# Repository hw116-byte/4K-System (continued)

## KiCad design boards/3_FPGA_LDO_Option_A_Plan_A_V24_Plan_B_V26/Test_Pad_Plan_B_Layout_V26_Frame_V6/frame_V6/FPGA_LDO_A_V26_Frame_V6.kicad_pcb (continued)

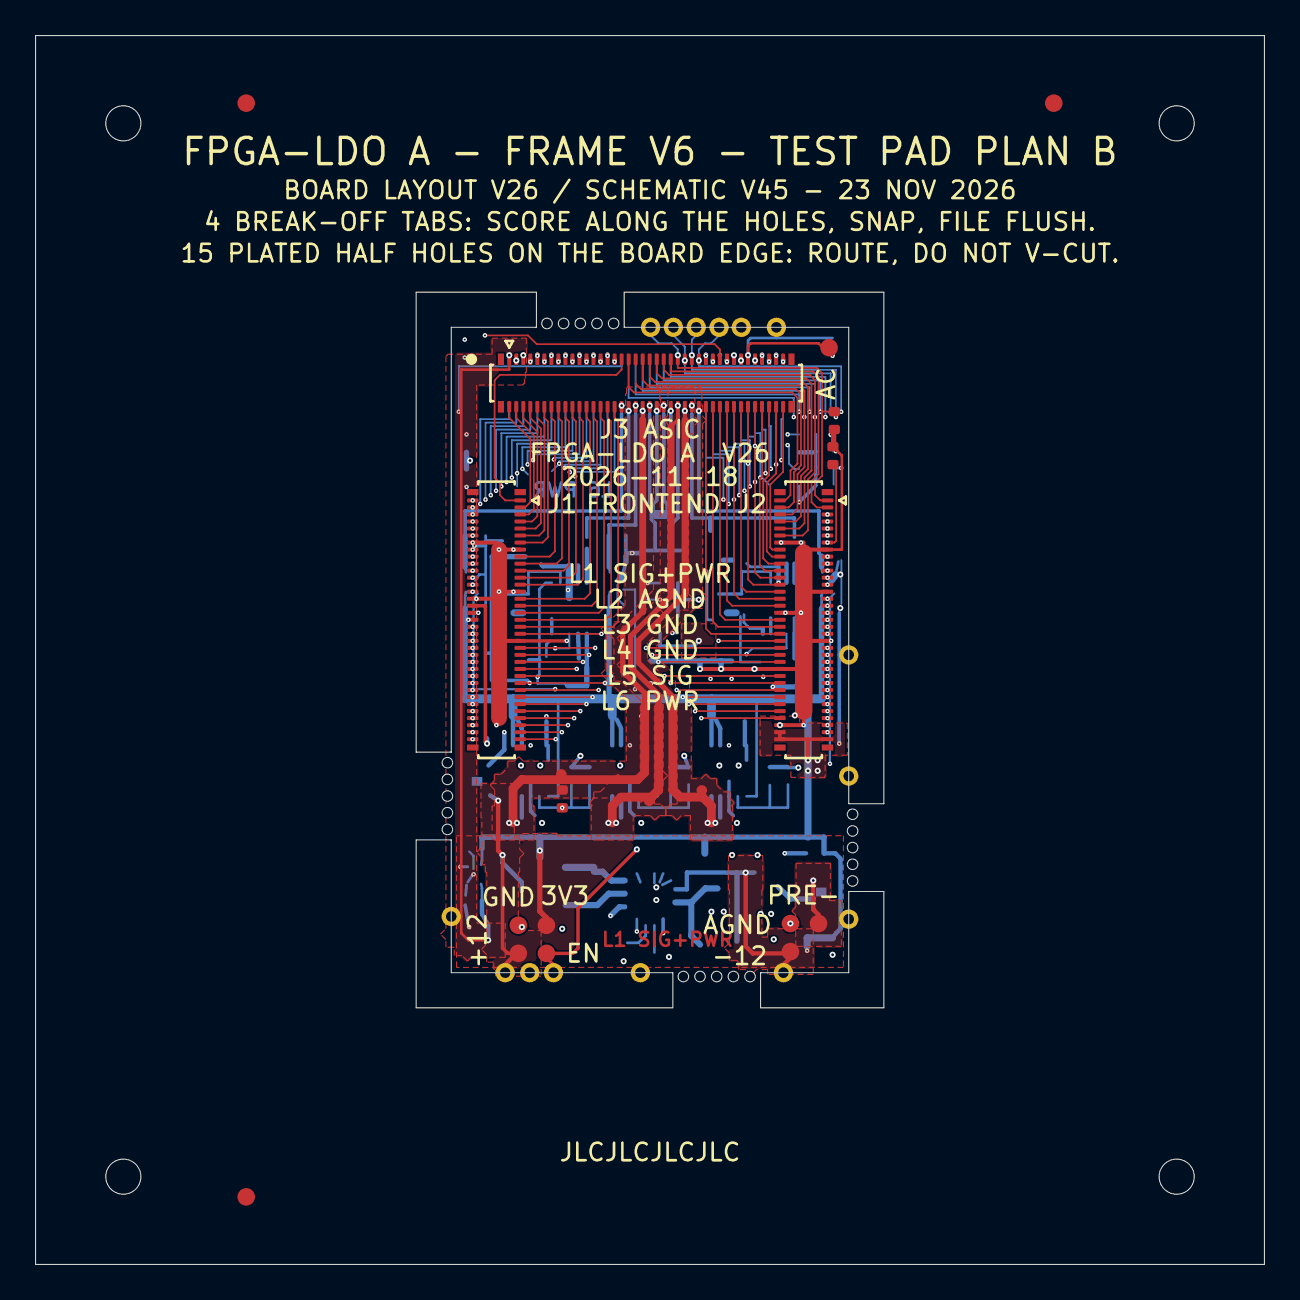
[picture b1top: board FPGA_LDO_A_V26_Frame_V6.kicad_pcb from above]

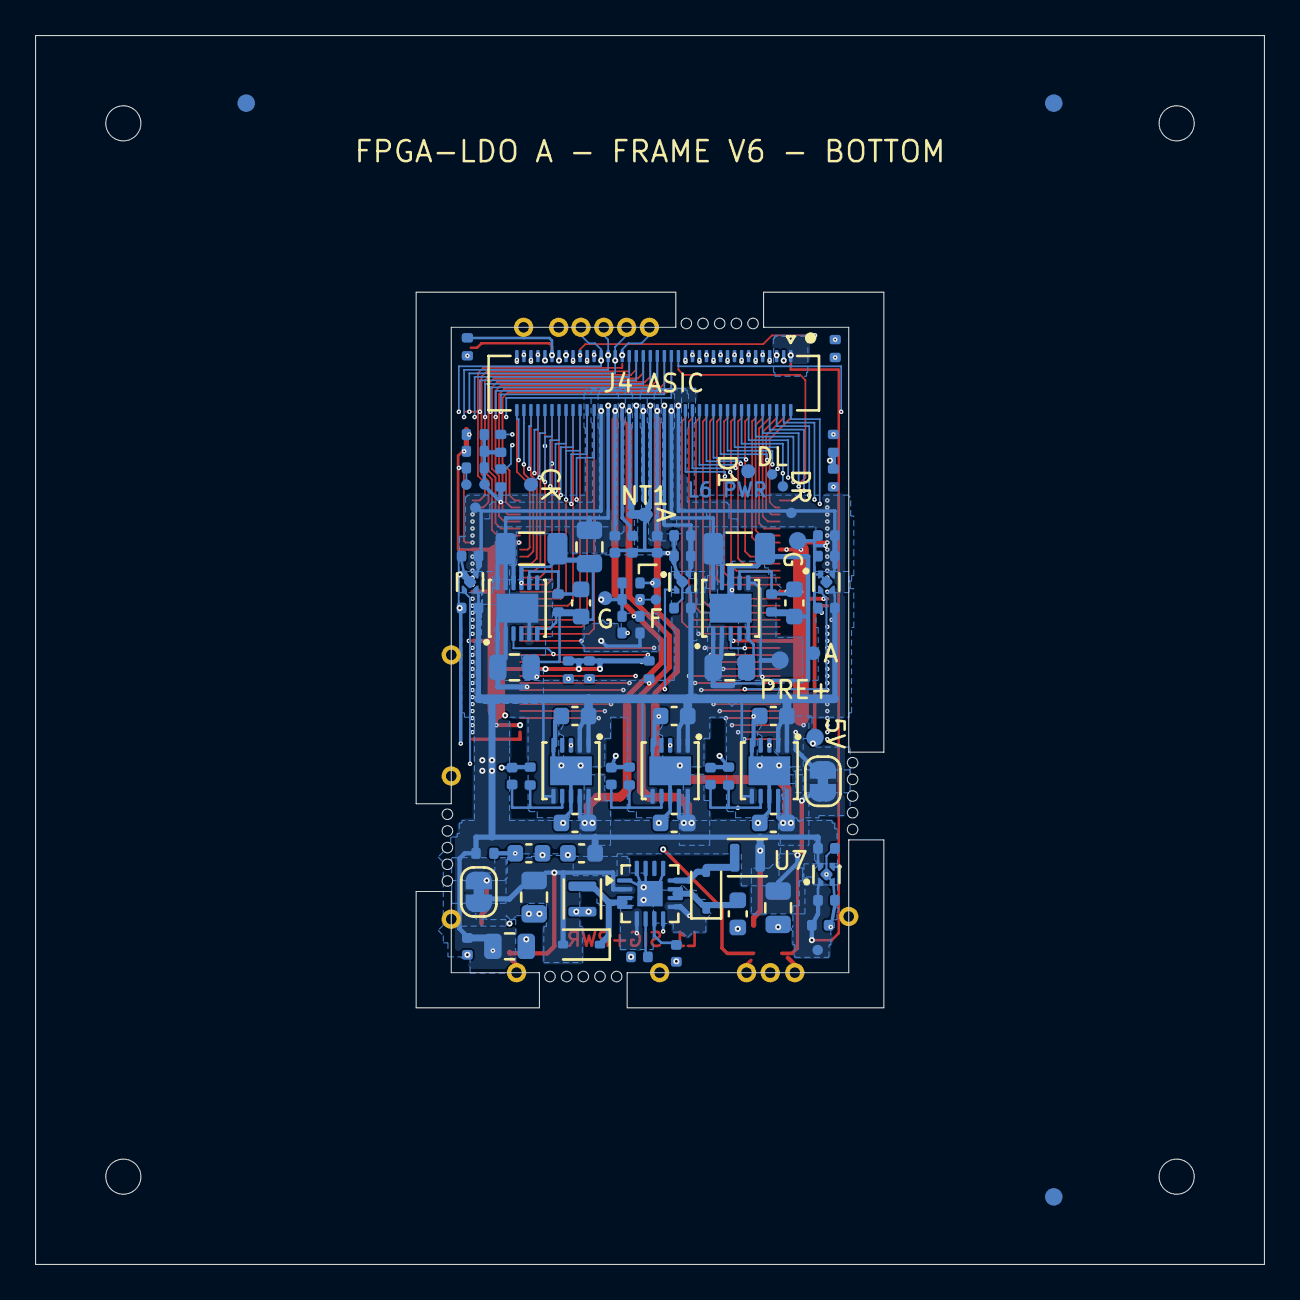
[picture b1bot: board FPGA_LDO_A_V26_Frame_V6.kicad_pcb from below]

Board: 6 copper layers, 70.0 x 70.0 mm, 142 parts (99 on the bottom side), 150 nets.

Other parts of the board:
FID1, FID2, FID3, FID4, FID5, FID6: fiducial 1.0 mm, mask opening 2.0 mm
MB1: mech tab N1, 5 x 0.60 mm holes
MB2: mech tab S1, 5 x 0.60 mm holes
MB3: mech tab W1, 5 x 0.60 mm holes
MB4: mech tab E1, 5 x 0.60 mm holes
TH1, TH2, TH3, TH4: tooling hole 2.0 mm, not plated

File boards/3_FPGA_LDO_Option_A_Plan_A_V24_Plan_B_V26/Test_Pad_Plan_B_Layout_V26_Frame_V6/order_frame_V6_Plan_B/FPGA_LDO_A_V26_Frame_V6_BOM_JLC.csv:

Comment,Designator,Footprint,JLCPCB Part #,Qty,Note
Samsung CL21A226MAYNNNE 22uF 25V X5R 0805,"C1,C14,C21",C_0805_2012Metric,C602037,3,
Samsung CL05B104KB54PNC 100nF 50V X7R 0402,C2,C_0402_1005Metric,C307331,1,
Samsung CL10A475KP8NNNC 4.7uF 10V X5R 0603,"C3,C11",C_0603_1608Metric,C1705,2,
Samsung CL10A105KA8NNNC 1uF 25V X5R 0603,"C15,C903,C1003",C_0603_1608Metric,C5673,3,
Samsung CL05B103KB5NNNC 10nF 50V X7R 0402,"C16,C17",C_0402_1005Metric,C15195,2,
Samsung CL05A105KP5NNNC 1uF 10V X5R 0402,"C51,C53,C54,C55,C56,C57,C203,C301,C302,C401,C402,C501,C502,C603,C701,C702,C803",C_0402_1005Metric,C14445,17,
Samsung CL10A106KP8NNNC 10uF 10V X5R 0603,"C201,C202,C601,C602,C801,C802",C_0603_1608Metric,C19702,6,
Samsung CL21A106KAYNNNE 10uF 25V X5R 0805,"C901,C1001,C1004",C_0805_2012Metric,C15850,3,
Samsung CL31A226KAHNNNE 22uF 25V X5R 1206,"C902,C1002",C_1206_3216Metric,C12891,2,
MCC B0540WS-TP 40V 0.5A Schottky SOD-323,"D11,D12",D_SOD-323,C668860,2,"Schematic V35 names this part (V34 named Diodes Inc. B0540WS-7, C98664, which cannot be ordered at JLC); it is the part of the 11 Nov 2026 cart. JLC library pad 1 is the ANODE for this part: the CPL angle is turned 180 deg against KiCad. Cathode positions are in the pin-1 table."
Hirose DF40C-70DP-0.4V(51),"J1,J2",Hirose_DF40C-70DP-0.4V_2x35-1MP_P0.4mm,C2692097,2,
Hirose DF40C-80DP-0.4V(51),J3,Hirose_DF40C-80DP-0.4V_2x40-1MP_P0.4mm,C294544,1,
Hirose DF40C-80DS-0.4V(51),J4,Hirose_DF40C-80DS-0.4V_2x40_P0.4mm,C312960,1,
TDK VLS201612HBX-6R8M-1 6.8uH 2.0x1.6x1.2mm,"L11,L12",L_Murata_DFE201610P,C501945,2,"Schematic V35 names this part (V34 named Murata DFE201610E-6R8M=P2, no JLC listing); it is the part of the 11 Nov 2026 cart. Isat 0.91 A, 1.2 mm high."
Uniroyal 0402WGF1002TCE 10k 1% 0402,"R1,R2,R3,R4,R5,R6,R16,R17,R18,R19,R20,R21,R22,R23,R24,R25,R26,R27,R28",R_0402_1005Metric,C25744,19,"R28 is new in layout V24: 10k from BOARD3_SPI_LATCH to GND, bottom side; the same part as R16-R27. JLC Basic part."
Uniroyal 0402WGF1502TCE 15k 1% 0402,"R201,R601",R_0402_1005Metric,C25756,2,
Uniroyal 0402WGF7501TCE 7.5k 1% 0402,R801,R_0402_1005Metric,C25918,1,
Uniroyal 0402WGF8062TCE 80.6k 1% 0402,"R901,R1001",R_0402_1005Metric,C25921,2,
Analog Devices LT3582EUD-12#PBF,U1,QFN-16-1EP_3x3mm_P0.5mm_EP1.45x1.45mm,C670975,1,Only the -12 version is acceptable (LT3582EUD-12#PBF or #TRPBF); no base LT3582 and no -5.
"Analog Devices LT3042EDD#TRPBF (same part as LT3042EDD#PBF, on tape and reel)","U2,U6,U8,U9",DFN-10-1EP_3x3mm_P0.5mm_EP1.65x2.38mm,C580010,4,
Texas Instruments TPS7A2015PDQNR,"U3,U4,U5,U7",Texas_X2SON-4_1x1mm_P0.65mm,C2862700,4,
Analog Devices LT3094EDD#PBF,U10,DFN-12-1EP_3x3mm_P0.45mm_EP1.65x2.38mm,C670492,1,
Uniroyal 0402WGF4702TCE 47k 1% 0402,R802,R_0402_1005Metric,C25792,1,"New in layout V22: minimum load of U8 (LT3042, 0.75 V REF_VCM), from ASIC_REF_VCM to AGND. JLC Basic part."

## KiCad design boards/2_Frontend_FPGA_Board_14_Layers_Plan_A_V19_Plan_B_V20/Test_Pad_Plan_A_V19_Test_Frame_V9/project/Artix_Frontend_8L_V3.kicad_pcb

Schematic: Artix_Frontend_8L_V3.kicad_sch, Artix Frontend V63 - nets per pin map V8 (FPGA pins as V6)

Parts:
C1, C2, C12, C13, C21, C22, C85, C86: 22uF; C_0603_1608Metric; Voltage 6.3 V; Tolerance 20%; MPN GRM188R60J226MEA0D; LCSC C77042
C3, C14, C23, C87: 22pF; C_0201_GRM03_Murata_0p22Gap; Voltage 50 V; Tolerance 2%; MPN GRM0335C1H220GA01D; LCSC C161417
C4, C89: 100uF; C_0805_2012Metric; Voltage 6.3 V; Tolerance 20%; MPN GRM21BR60J107ME15L; not fitted
C5, C6, C25, C36, C37, C51, C54, C96, C107: 4.7uF; C_0201_GRM03_Murata_0p22Gap; Voltage 6.3 V; Tolerance 20%; MPN GRM035R60J475ME15D; LCSC C335103
C7, C8, C9, C11, C18, C19, C20, C26, C27, C28, C29, C32, C33, C34, C35, C38, C39, C40, C52, C53, C55, C56, C57, C58, C80, C91, C92, C93, C97, C98, C99, C100: 470nF; C_0201_GRM03_Murata_0p22Gap; Voltage 6.3 V; Tolerance 20%; MPN GRM033R60J474ME90D; LCSC C88915
C10: 47uF; C_0805_2012Metric; Voltage 6.3 V; Tolerance 20%; MPN GRM21BR60J476ME15L; LCSC C77072
C15: 47uF; C_0805_2012Metric; Voltage 6.3 V; Tolerance 20%; MPN CC0805MKX5R5BB476; LCSC C109461
C16, C17, C24, C30, C31, C43, C44, C45, C47, C48, C49, C90, C94, C95, C101: 4.7uF; C_0402_1005Metric; Voltage 6.3 V; Tolerance 20%; MPN GRM155R60J475ME47D; LCSC C82453
C42: 47uF; C_0805_2012Metric; Voltage 6.3 V; Tolerance 20%; MPN GRM219R60J476ME44D; LCSC C471380
C46, C50: 10nF; C_0201_GRM03_Murata_0p22Gap; Voltage 10 V; Tolerance 10%; MPN GRM033R71A103KA01D; LCSC C76941
C59: 47uF; C_0805_2012Metric; Voltage 6.3 V; Tolerance 20%; MPN CC0805MKX5R5BB476; not fitted
C60, C63, C78, C79, C81, C82, C83, C88, C105, C106, C209: 100nF; C_0201_GRM03_Murata_0p22Gap; Voltage 10 V; Tolerance 10%; MPN GRM033R61A104KE15D; LCSC C76934
C61, C84: 1uF; C_0402_1005Metric; Voltage 10 V; Tolerance 10%; MPN GRM155C81A105KA12D; LCSC C162161
C62: 220nF; C_0201_GRM03_Murata_0p22Gap; Voltage 6.3 V; Tolerance 10%; MPN GRM033R60J224KE15D; LCSC C76931
C75, C76, C102, C104: 22uF / 6.3V; C_0603_1608Metric; Voltage 6.3 V; Tolerance 20%; MPN GRM188R60J226MEA0D; LCSC C77042
C77: 22nF / 16V; C_0201_GRM03_Murata_0p22Gap; Voltage 16V; Tolerance 10%; MPN GRM033R61C223KE84D; LCSC C161473
C103: 470nF / 6.3V; C_0201_GRM03_Murata_0p22Gap; Voltage 6.3 V; Tolerance 20%; MPN GRM033R60J474ME90D; LCSC C88915
C206, C207, C208: 22uF / 10V; C_0805_2012Metric; Voltage 10 V; Tolerance 20%; MPN GRM21BR61A226ME44L; LCSC C441864
J1, J2: DF40C-70DS-0.4V(51); Hirose_DF40C-70DS-0.4V_2x35_P0.4mm; MPN DF40C-70DS-0.4V(51); LCSC C294854
J3: Micro-HDMI 467651001; Molex_MicroHDMI_46765_1xxx; MPN 467651001; LCSC C563878
L1, L2, L3, L4: MPZ0603S121HT000; TDK_MPZ0603S121HT000_0201_Land_0p25x0p30_Gap0p30; MPN MPZ0603S121HT000; LCSC C695597
R1, R4, R5, R41, R55: 200k; R_0201_ERA1A_Panasonic_0p30Gap; Tolerance 1%; Voltage_rating 25 V; MPN RC0201FR-07200KL; LCSC C138163
R2: 301k; R_0201_ERA1A_Panasonic_0p30Gap; Tolerance 1%; Voltage_rating 25 V; MPN RC0201FR-07301KL; LCSC C77621
R3, R9, R19, R22, R38, R43: 4.99k; R_0201_ERA1A_Panasonic_0p30Gap; Tolerance 1%; Voltage_rating 25 V; MPN RC0201FR-074K99L; LCSC C273265
R7: 150k; R_0402_TE_CPF_Reflow_0p50Gap; Tolerance 0.1%; Voltage_rating 25 V; MPN RT0402BRD07150KL; LCSC C852538
R8: 100k; R_0402_TE_CPF_Reflow_0p50Gap; Tolerance 0.1%; Voltage_rating 25 V; MPN CPF0402B100KE; LCSC C4015434
R10: 1.3k; R_0201_ERA1A_Panasonic_0p30Gap; Tolerance 1%; Voltage_rating 25 V; MPN 0201WMF1301TEE; LCSC C473569
R11, R14: 4.99k; R_0201_ERA1A_Panasonic_0p30Gap; Tolerance 0.1%; Voltage_rating 25 V; MPN RT0201BRD074K99L; LCSC C852255
R13: 2.49k; R_0201_ERA1A_Panasonic_0p30Gap; Tolerance 0.1%; Voltage_rating 25 V; MPN TNPW02012K49BEED; LCSC C1870640
R16: 100R; R_0201_ERA1A_Panasonic_0p30Gap; Tolerance 0.1%; Voltage_rating 25 V; MPN ERA1AEB101C; LCSC C490806
R17, R18: 4.7k; R_0201_ERA1A_Panasonic_0p30Gap; Tolerance 1%; Voltage_rating 25 V; MPN RC0201FR-074K7L; LCSC C138135
R20, R21, R49, R50: 4.7k; R_0201_ERA1A_Panasonic_0p30Gap; Tolerance 1%; MPN RC0201FR-074K7L; LCSC C138135
R25: 470R; R_0201_ERA1A_Panasonic_0p30Gap; Tolerance 1%; Voltage_rating 25 V; MPN RC0201FR-07470RL; LCSC C295802
R27: 1k; R_0201_ERA1A_Panasonic_0p30Gap; Tolerance 1%; MPN RC0201FR-071KL; LCSC C138165
R37: 24k / 1%; R_0201_ERA1A_Panasonic_0p30Gap; Tolerance 1%; Voltage_rating 25 V; MPN 0201WMF2402TEE; LCSC C270353
R42: 150k; R_0201_ERA1A_Panasonic_0p30Gap; Tolerance 1%; Voltage_rating 25 V; MPN RC0201FR-07150KL; LCSC C274346
R44: 150R; R_0201_0603Metric; Tolerance 1%; Voltage_rating 25 V; MPN RC0201FR-07150RL; LCSC C295773
R45: 4.64k; R_0402_1005Metric; Tolerance 0.1%; MPN RT0402BRD074K64L; LCSC C705067
R46, R47, R48: 10k; R_0201_ERA1A_Panasonic_0p30Gap; Tolerance 0.1%; MPN ERA1AEB103C; LCSC C490808
R51, R52, R53: 47k; R_0201_ERA1A_Panasonic_0p30Gap; Tolerance 1%; MPN RC0201FR-0747KL; LCSC C138139
R54: 22k; R_0201_ERA1A_Panasonic_0p30Gap; Tolerance 1%; MPN RC0201FR-0722KL; LCSC C474416
R57: 10k; R_0201_ERA1A_Panasonic_0p30Gap; Tolerance 1%; MPN RC0201FR-0710KL; LCSC C106225
R58: 4.99k; R_0201_ERA1A_Panasonic_0p30Gap; Tolerance 1%; MPN RC0201FR-074K99L; LCSC C273265
R59: 200k; R_0201_ERA1A_Panasonic_0p30Gap; Tolerance 1%; MPN RC0201FR-07200KL; LCSC C138163
R60: 44.2k; R_0201_ERA1A_Panasonic_0p30Gap; Tolerance 1%; MPN AC0201FR-0744K2L; LCSC C226551
R61, R62, R64: 100R; R_0201_ERA1A_Panasonic_0p30Gap; Tolerance 0.1%; MPN ERA1AEB101C; LCSC C490806
R63: 680R; R_0201_0603Metric; Tolerance 1%; MPN AC0201FR-07680RL; LCSC C4103963
TP1, TP2, TP3, TP4, TP5, TP6, TP7, TP8, TP9, TP10, TP11, TP12, TP13, TP14, TP15, TP16, TP17, TP18, TP19, TP20, TP21, TP22, TP23, TP24, TP25, TP26, TP27, TP28, TP29, TP30, TP31, TP32, TP33, TP34, TP35, TP36, TP37, TP38, TP39, TP40, TP41, TP42, TP43, TP44, TP45, TP46, TP47: 0.6mm COPPER; TestPoint_Pad_D0.6mm_Edge_NoPaste
U1: XC7A35T-2CSG325C; Xilinx_CSG325; MPN XC7A35T-2CSG325C; LCSC C1521720
U2, U3, U4, U13, U16: MPM3833CGRH; MPS_QFN-18_2.5x3.5mm_MPM3833C; MPN MPM3833CGRH-Z; LCSC C6306422
U5, U6: TPS74801DRCR; VSON-10-1EP_3x3mm_P0.5mm_EP1.65x2.4mm; MPN TPS74801DRCR; LCSC C105263
U7: W25Q64JWUUIQ; Winbond_USON8_4x3mm_UU; MPN W25Q64JWUUIQ; LCSC C6604692
U8: SN74AVC4T774RSVR / SPI x1; TI_RSV_UQFN16_1.8x2.6mm_P0.4mm; MPN SN74AVC4T774RSVR; LCSC C779392
U10: MP5077GG-Z; MPS_MP5077_QFN12_2x2mm_P0.4mm; MPN MP5077GG-Z; LCSC C3215595
U11: 74AUP2G07GM / dual reset OD; Nexperia_SOT886_XSON6_1x1.45mm; MPN 74AUP2G07GM,115; LCSC C546047
U12: TPS389001 / timed rail-ready reset; TI_DSE0006A_WSON6_1p5x1p5_P0p5_Manufacturer; MPN TPS389001DSER; LCSC C1509297
U14: SN74AUP1G14 / SPI OE; Texas_USON-6_1x1.45mm_P0.5mm_SMD; MPN SN74AUP1G14DRYR; LCSC C2865597
U15: SN74AXC1T45DRLR; SOT-563; MPN SN74AXC1T45DRLR; LCSC C191003
U17, U18: TPD4E02B04DQAR; USON-10_2.5x1.0mm_P0.5mm; MPN TPD4E02B04DQAR; LCSC C106794
Y1: AX3DAF1-125.0000T3 / 125 MHz; Abracon_AX3_3225_6pin; Voltage 3.3 V filtered from SWITCHED_3V3 by L4; MPN AX3DAF1-125.0000T3; LCSC C1670018
Y2: OT201625MJBA4SL / 25 MHz / 1.8 V; YXC_SMD2016-4P_2.0x1.6mm; MPN OT201625MJBA4SL; LCSC C669080

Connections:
1V4_GTP_IN: C43.2, C47.2, C86.1, C87.1, R41.1, TP16.1 (PAD_1), U5.1 (IN), U5.2 (IN), U6.1 (IN), U6.2 (IN), U13.3 (OUT_S), U13.8 (OUT), U13.9 (OUT), U13.10 (OUT)
/ASIC1_CLK32MHz_Out: J2.59, U1.R2 (L13P_T2_MRCC)
/ASIC1_DATA1: J2.21, U1.U2 (L15P_T2_DQS)
/ASIC1_DATA2: J2.64, U1.J4 (L2N_T0)
/ASIC1_DATA3: J2.62, U1.K2 (L3P_T0_DQS)
/ASIC1_DATA4: J2.60, U1.K1 (L3N_T0_DQS)
/ASIC1_DATA5: J2.57, U1.M1 (L7N_T1)
/ASIC1_DATA6: J2.55, U1.N1 (L9P_T1_DQS)
/ASIC1_DATA7: J2.53, U1.P1 (L9N_T1_DQS)
/ASIC1_DATA8: J2.51, U1.L3 (L5N_T0)
/ASIC1_READ: J2.49, U1.L2 (L4N_T0)
/ASIC1_SYNC: J2.61, U1.J5 (L2P_T0)
/ASIC2_CLK32MHz_Out: J1.63, TP29.1 (PAD_1), U1.D13 (L11P_T1_SRCC)
/ASIC2_DATA1: J1.70, U1.A17 (L15N_T2_DQS_ADV_B)
/ASIC2_DATA2: J1.51, U1.E15 (L13P_T2_MRCC)
/ASIC2_DATA3: J1.53, U1.D16 (L14N_T2_SRCC)
/ASIC2_DATA4: J1.55, U1.D15 (L13N_T2_MRCC)
/ASIC2_DATA5: J1.65, U1.B14 (L10P_T1_AD11P)
/ASIC2_DATA6: J1.67, U1.A15 (L10N_T1_AD11N)
/ASIC2_DATA7: J1.69, U1.A14 (L8N_T1_AD10N)
/ASIC2_DATA8: J1.38, U1.H17 (L23P_T3_FOE_B)
/ASIC2_READ: J1.40, U1.H18 (L23N_T3_FWE_B)
/ASIC2_SYNC: J1.61, TP33.1 (PAD_1), U1.B15 (L9N_T1_DQS_AD3N)
/ASIC3_4_TOP_SPI_CLK: J2.37, U1.P3 (L12N_T1_MRCC)
/ASIC3_4_TOP_SPI_LATCH: J2.35, U1.R7 (L22P_T3)
/ASIC3_CLK32MHz_Out: J2.25, U1.P4 (L12P_T1_MRCC)
/ASIC3_DATA1: J2.47, U1.L5 (L6P_T0)
/ASIC3_DATA2: J2.45, U1.M6 (L8P_T1)
/ASIC3_DATA3: J2.43, U1.N2 (L11N_T1_SRCC)
/ASIC3_DATA4: J2.39, U1.N6 (L8N_T1)
/ASIC3_DATA5: J2.23, U1.T2 (L14N_T2_SRCC)
/ASIC3_DATA6: J2.42, U1.D9 (L2P_T0_AD8P)
/ASIC3_DATA7: J1.39, U1.D14 (L12N_T1_MRCC)
/ASIC3_DATA8: J1.43, U1.G15 (L21P_T3_DQS)
/ASIC3_READ: J1.45, U1.F14 (L22N_T3_A16)
/ASIC3_SPI_DL: J2.33, U1.R5 (L21P_T3_DQS)
/ASIC3_SPI_DR: J2.31, U1.T7 (L22N_T3)
/ASIC3_SYNC: J2.29, U1.T3 (L17N_T2)
/ASIC4_CLK32MHz_Out: J1.56, U1.E16 (L14P_T2_SRCC)
/ASIC4_DATA1: J1.47, U1.F15 (L21N_T3_DQS_A18)
/ASIC4_DATA2: J1.49, U1.E13 (L12P_T1_MRCC)
/ASIC4_DATA3: J1.44, U1.G17 (L19P_T3_A22)
/ASIC4_DATA4: J1.46, U1.F17 (L24P_T3_RS1)
/ASIC4_DATA5: J1.58, U1.D18 (L17N_T2_A25)
/ASIC4_DATA6: J1.60, U1.C18 (L18N_T2_A23)
/ASIC4_DATA7: J1.62, U1.C17 (L18P_T2_A24)
/ASIC4_DATA8: J1.64, U1.B17 (L16N_T2_A27)
/ASIC4_READ: J1.68, U1.B16 (L15P_T2_DQS)
/ASIC4_SPI_DL: J1.48, U1.F18 (L19N_T3_A21_VREF)
/ASIC4_SPI_DR: J1.52, U1.E18 (L24N_T3_RS0)
/ASIC4_SYNC: J1.54, U1.E17 (L17P_T2_A26)
/ASIC5_CLK32MHz_Out: J2.12, U1.R3 (L14P_T2_SRCC)
/ASIC5_DATA1: J2.5, U1.V4 (L18N_T2)
/ASIC5_DATA2: J2.7, U1.U1 (L15N_T2_DQS)
/ASIC5_DATA3: J2.9, U1.U4 (L18P_T2)
/ASIC5_DATA4: J2.11, U1.U5 (L20N_T3)
/ASIC5_DATA5: J2.10, U1.T5 (L21N_T3_DQS)
/ASIC5_DATA6: J2.8, U1.T4 (L17P_T2)
/ASIC5_DATA7: J2.6, U1.U6 (L20P_T3)
/ASIC5_DATA8: J2.4, U1.U7 (L23P_T3)
/ASIC5_READ: J2.2, U1.V3 (L16P_T2)
/ASIC5_SYNC: J2.3, U1.V2 (L16N_T2)
/ASIC6_CLK32MHz_Out: J1.16, U1.R16 (L14P_T2_SRCC)
/ASIC6_DATA1: J1.1, U1.V16 (L18P_T2_A12_D28)
/ASIC6_DATA2: J1.28, U1.K18 (L3N_T0_DQS_EMCCLK)
/ASIC6_DATA3: J1.26, U1.L18 (L4N_T0_D05)
/ASIC6_DATA4: J1.24, U1.M17 (L7N_T1_D10)
/ASIC6_DATA5: J1.12, U1.R18 (L15P_T2_DQS_RDWR_B)
/ASIC6_DATA6: J1.10, U1.R17 (L14N_T2_SRCC)
/ASIC6_DATA7: J1.8, U1.T18 (L15N_T2_DQS_DOUT_CSO_B)
/ASIC6_DATA8: J1.6, U1.T17 (L16P_T2_CSI_B)
/ASIC6_READ: J1.4, U1.U17 (L16N_T2_A15_D31)
/ASIC6_SYNC: J1.18, U1.P18 (L10N_T1_D15)
/ASIC7_8_TOP_SPI_CLK: J2.24, TP43.1 (PAD_1), U1.N4 (L10N_T1)
/ASIC7_8_TOP_SPI_LATCH: J2.26, TP42.1 (PAD_1), U1.L4 (L5P_T0)
/ASIC7_CLK32MHz_Out: J2.36, U1.N3 (L11P_T1_SRCC)
/ASIC7_DATA1: J2.16, U1.R1 (L13N_T2_MRCC)
/ASIC7_DATA2: J2.18, U1.R6 (IO25)
/ASIC7_DATA3: J2.20, U1.P5 (L19N_T3_VREF)
/ASIC7_DATA4: J2.22, U1.P6 (L19P_T3)
/ASIC7_DATA5: J2.38, TP38.1 (PAD_1), U1.K3 (L4P_T0)
/ASIC7_DATA6: J2.40, U1.U9 (L24P_T3_A01_D17)
/ASIC7_DATA7: J1.37, U1.H16 (L20P_T3_A20)
/ASIC7_DATA8: J1.35, U1.V13 (L21N_T3_DQS_A06_D22)
/ASIC7_READ: J1.33, U1.T12 (L22P_T3_A05_D21)
/ASIC7_SPI_DL: J2.28, U1.M4 (L10P_T1)
/ASIC7_SPI_DR: J2.30, U1.M2 (L7P_T1)
/ASIC7_SYNC: J2.32, TP41.1 (PAD_1), U1.M5 (L6N_T0_VREF)
/ASIC8_CLK32MHz_Out: J1.13, U1.P15 (L11P_T1_SRCC)
/ASIC8_DATA1: J1.31, U1.U12 (L22N_T3_A04_D20)
/ASIC8_DATA2: J1.29, U1.K17 (L4P_T0_D04)
/ASIC8_DATA3: J1.25, U1.K15 (L5N_T0_D07)
/ASIC8_DATA4: J1.23, U1.L14 (IO0)
/ASIC8_DATA5: J1.11, TP47.1 (PAD_1), U1.R13 (L19P_T3_A10_D26)
/ASIC8_DATA6: J1.9, U1.T15 (L13N_T2_MRCC)
/ASIC8_DATA7: J1.7, U1.U14 (L20P_T3_A08_D24)
/ASIC8_DATA8: J1.5, U1.U16 (L17N_T2_A13_D29)
/ASIC8_READ: J1.3, U1.U15 (L17P_T2_A14_D30)
/ASIC8_SPI_DL: J1.21, U1.M16 (L7P_T1_D09)
/ASIC8_SPI_DR: J1.19, U1.N16 (L9P_T1_DQS)
/ASIC8_SYNC: J1.17, U1.P16 (L11N_T1_SRCC)
/BOARD3_SPI_LATCH: J1.36, U1.V14 (L20N_T3_A07_D23)
/CABLE_CLK_N: J3.8 (TX1_REC_N), R61.2, U1.R15 (L12N_T1_MRCC), U17.2 (IO2), U17.9 (IO2_FT)
/CABLE_CLK_P: J3.6 (TX1_REC_P), R61.1, U1.P14 (L12P_T1_MRCC), U17.1 (IO1), U17.10 (IO1_FT)
/CABLE_CMDSYNC_N: J3.11 (TX2_REC_N), R62.2, U1.N14 (L8N_T1_D12), U17.5 (IO4), U17.6 (IO4_FT)
/CABLE_CMDSYNC_P: J3.9 (TX2_REC_P), R62.1, U1.M14 (L8P_T1_D11), U17.4 (IO3), U17.7 (IO3_FT)
/CABLE_SYNC_N: J3.14 (GPIO_CMD_N), R64.2, U1.A9 (L3N_T0_DQS_AD1N), U18.2 (IO2), U18.9 (IO2_FT)
/CABLE_SYNC_P: J3.12 (GPIO_CMD_P), R64.1, U1.B9 (L3P_T0_DQS_AD1P), U18.1 (IO1), U18.10 (IO1_FT)
/CLK25_RAW: R44.1, Y2.3 (OUT)
/CLK25_VDD: C88.1, L3.2, Y2.1 (OE), Y2.4 (VDD)
/FB_GTP_1V4: C87.2, R41.2, R42.1, U13.2 (FB)
/FB_VIN_3V3: R59.2, R60.1, U16.2 (FB)
/FE_RESET_SHARED: J2.54, U1.D8 (L1P_T0_AD0P)
/IMP_TST_SHARED: J2.56, U1.C8 (L1N_T0_AD0N)
/STIM_CHIP1_SPI_DL: J2.46, U1.C11 (L4P_T0)
/STIM_CHIP1_SPI_DR: J2.44, U1.G14 (L22P_T3_A17)
/STIM_CHIP2_SPI_DL: J1.57, U1.C14 (L9P_T1_DQS_AD3P)
/STIM_CHIP3_SPI_DL: J2.17, U1.V7 (L24N_T3)
/STIM_CHIP4_SPI_DR: J1.20, U1.N18 (L10P_T1_D14)
BOARD1_CLK: J1.42, U1.G16 (L20N_T3_A19)
BOARD1_SPI_CLK: J2.52, U1.D10 (IO0)
BOARD1_SPI_LATCH: J2.48, U1.D11 (L6P_T0)
BOARD3_CLK: J1.2, U1.V17 (L18N_T2_A11_D27)
BOARD3_SPI_CLK: J2.13, U1.V8 (L24P_T3)
BOOT_RAILS_PG_3V3: R9.2, TP10.1 (PAD_1), U4.12 (PG), U5.3 (PG), U6.5 (EN), U12.3 (MR_PG)
BOOT_RESET_N: R47.2, TP28.1 (PAD_1), U11.1 (1A_RESET_N), U11.3 (2A_RESET_N), U12.6 (RESET_N_OD), U14.2 (A_RESET_N)
CABLE_TARGET_SENSE: J3.1 (SENSE), R27.2
CHIP_RESET_SHARED: J2.58, TP34.1 (PAD_1), U1.C9 (L2N_T0_AD8N)
CLK25_PL: R44.2, R63.1, TP44.1 (PAD_1), U1.T14 (L13P_T2_MRCC)
EN_GTPWR_1V5: R58.2, TP45.1 (PAD_1), U1.M15 (L6N_T0_D08_VREF), U15.3 (A)
EN_GTPWR_3V3: R57.1, U13.4 (EN), U15.4 (B)
FLASH_CS_N_1V8: R22.2, U7.1 (CE#), U8.11 (B2_CS)
FLASH_DQ0_1V8: R53.2, TP25.1 (PAD_1), U7.5 (SI / DQ0), U8.10 (B3_MOSI)
FLASH_DQ1_1V8: R51.1, U7.2 (SO / DQ1), U8.9 (B4_MISO)
FLASH_HOLD_N_1V8: R21.2, U7.7 (HOLD# / DQ3)
FLASH_READY_SENSE: R45.2, R46.1, U12.1 (SENSE_DIV)
FLASH_SCK_1V8: R52.1, U7.6 (SCK), U8.12 (B1_SCK)
FLASH_TRANSLATOR_OE_N: R48.2, U8.7 (OE_N), U14.4 (Y_OE_N)
FLASH_WP_N_1V8: R20.2, U7.3 (WP# / DQ2)
FPGA_DONE: R38.2, TP12.1 (PAD_1), U1.F12 (DONE_0)
FPGA_INIT_B: R18.2, TP11.1 (PAD_1), U1.T10 (INIT_B_0), U11.4 (2Y_INIT_OD)
FPGA_JTAG_TCK: J3.17 (TCK), U1.F8 (TCK_0)
FPGA_JTAG_TDI: J3.15 (TDI), U1.T9 (TDI_0)
FPGA_JTAG_TDO: J3.18 (TDO), U1.T8 (TDO_0)
FPGA_JTAG_TMS: J3.2 (TMS), U1.R8 (TMS_0)
FPGA_PROGRAM_B: R17.2, TP35.1 (PAD_1), U1.P10 (PROGRAM_B_0), U11.6 (1Y_PROGRAM_OD)
FPGA_PUDC_B: R25.2, U1.J18 (L3P_T0_DQS_PUDC_B)
FPGA_QSPI_CCLK: R49.2, TP30.1 (PAD_1), U1.E8 (CCLK_0), U8.1 (A1_CCLK)
FPGA_QSPI_CS_N: R19.2, U1.L15 (L6P_T0_FCS_B), U8.2 (A2_CS)
FPGA_QSPI_DQ0: R50.2, U1.K16 (L1P_T0_D00_MOSI), U8.3 (A3_MOSI)
FPGA_QSPI_DQ1: R54.1, U1.L17 (L1N_T0_D01_DIN), U8.4 (A4_MISO)
GND: C1.2, C2.2, C4.2, C5.2, C6.2, C7.2, C8.2, C9.2, C10.2, C11.2, C12.2, C13.2, C15.2, C16.2, C17.2, C18.2, C19.2, C20.2, C21.2, C22.2, C24.2, C25.2, C26.2, C27.2, C28.2, C29.2, C30.2, C31.2, C32.2, C33.2, C34.2, C35.2, C36.2, C37.2, C38.2, C39.2, C40.2, C42.2, C43.1, C44.2, C45.2, C46.2, C47.1, C48.2, C49.2, C50.2, C51.2, C52.2, C53.2, C54.2, C55.2, C56.2, C58.2, C59.2, C60.2, C61.2, C62.2, C63.2, C75.2, C76.2, C77.2, C80.2, C81.2, C82.2, C83.2, C84.2, C85.2, C86.2, C88.2, C89.2, C90.2, C91.2, C92.2, C93.2, C94.2, C95.2, C96.2, C97.2, C98.2, C99.2, C100.2, C101.2, C102.2, C103.2, C104.2, C105.2, C106.2, C107.2, C206.2, C207.2, C208.2, C209.2, J1.14, J1.15, J1.27, J1.30, J1.34, J1.41, J1.50, J1.66, J2.14, J2.15, J2.27, J2.34, J2.41, J2.50, J2.66, J3.4 (GND), J3.7 (GND), J3.10 (GND), J3.13 (GND), J3.16 (GND), J3.SH (SHIELD), L2.1, R2.2, R5.2, R8.2, R11.2, R14.2, R37.2, R42.2, R46.2, R51.2, R52.2, R54.2, R55.2, R57.2, R60.2, R63.2, TP1.1 (PAD_1), TP13.1 (PAD_1), TP15.1 (PAD_1), TP17.1 (PAD_1), TP18.1 (PAD_1), TP20.1 (PAD_1), TP21.1 (PAD_1), TP22.1 (PAD_1), TP26.1 (PAD_1), TP27.1 (PAD_1), TP31.1 (PAD_1), TP32.1 (PAD_1), TP36.1 (PAD_1), TP39.1 (PAD_1), TP40.1 (PAD_1), TP46.1 (PAD_1), U1.A1 (GND_[75_balls]), U1.A3 (MGTPRXN1_216), U1.A4 (MGTPRXP1_216), U1.A5 (GND), U1.A7 (GND), U1.A8 (GND), U1.A11 (GND), U1.A18 (GND), U1.B3 (GND), U1.B7 (GND), U1.B8 (GND), U1.B18 (GND), U1.C2 (GND), U1.C3 (MGTPRXN2_216), U1.C4 (MGTPRXP2_216), U1.C6 (GND), U1.C7 (GND), U1.C15 (GND), U1.D3 (GND), U1.D4 (GND), U1.D7 (GND), U1.D12 (GND), U1.E2 (GND), U1.E3 (MGTPRXN0_216), U1.E4 (MGTPRXP0_216), U1.E6 (GND), U1.E7 (GND), U1.E9 (GND), U1.E12 (CFGBVS_0), U1.F4 (GND), U1.F6 (GND), U1.F10 (GND), U1.F13 (M2_0), U1.F16 (GND), U1.G1 (GND), U1.G3 (MGTPRXN3_216), U1.G4 (MGTPRXP3_216), U1.G5 (GND), U1.G6 (GND), U1.G7 (GND), U1.G9 (GND), U1.G11 (GND), U1.G13 (GND), U1.H3 (GND), U1.H4 (GND), U1.H5 (GND), U1.H6 (GND), U1.H8 (GND), U1.H10 (GND), U1.H12 (GND), U1.J1 (GND), U1.J2 (GND), U1.J3 (GND), U1.J7 (GND), U1.J11 (GND), U1.J13 (GND), U1.J17 (GND), U1.K4 (GND), U1.K8 (GND)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
GNDADC_XADC: C57.2, L2.2, U1.J9 (GNDADC_0), U1.K9 (VREFN_0), U1.K10 (VP_0), U1.L9 (VN_0), U1.L10 (VREFP_0)
GTP_REFCLK1_N: C79.2, U1.B5 (MGTREFCLK1N_216)
GTP_REFCLK1_P: C78.2, U1.B6 (MGTREFCLK1P_216)
GTP_TX0_N: J3.3 (TX0_REC_P), U1.H1 (MGTPTXN0_216)
GTP_TX0_P: J3.5 (TX0_REC_N), U1.H2 (MGTPTXP0_216)
MGTAVCC_1V0: C45.1, C51.1, C52.1, C53.1, R10.1, TP7.1 (PAD_1), U1.B4 (MGTAVCC), U1.C5 (MGTAVCC), U1.E5 (MGTAVCC), U1.F5 (MGTAVCC), U5.9 (OUT), U5.10 (OUT)
MGTAVTT_1V2: C49.1, C54.1, C55.1, C56.1, R13.1, R16.1, TP8.1 (PAD_1), U1.A2 (MGTAVTT), U1.C1 (MGTAVTT), U1.E1 (MGTAVTT), U1.F3 (MGTAVTT), U1.G2 (MGTAVTT), U6.9 (OUT), U6.10 (OUT)
unnamed: R16.2, U1.A6 (MGTRREF_216)
unnamed: C3.2, R1.2, R2.1, U2.2 (FB)
unnamed: C14.2, R4.2, R5.1, R55.1, U3.2 (FB)
unnamed: C23.2, R7.2, R8.1, U4.2 (FB)
unnamed: R10.2, R11.1, U5.8 (FB)
unnamed: C46.1, U5.7 (SS)
unnamed: R13.2, R14.1, U6.8 (FB)
unnamed: C50.1, U6.7 (SS)
unnamed: R37.1, U10.4 (ILIM)
unnamed: C77.1, U10.5 (SS)
unnamed: C84.1, U12.5 (CT)
OSC125_3V3: C80.1, C81.1, L4.2, TP24.1 (PAD_1), Y1.1 (OE), Y1.6 (VDD)
OSC125_N: C79.1, Y1.5 (OUTN)
OSC125_P: C78.1, Y1.4 (OUTP)
PG_AUX_1V8: TP19.1 (PAD_1), U3.12 (PG), U4.4 (EN)
PG_CORE_1V0: R3.2, TP23.1 (PAD_1), U2.12 (PG), U3.4 (EN), U10.1 (EN)
PG_GTP_1V4: R43.2, U5.5 (EN), U13.12 (PG)
STIM_CHB_SHARED: J2.1, U1.V9 (L24N_T3_A00_D16)
STIM_CHIP2_SPI_DR: J1.59, U1.C16 (L16P_T2_A28)
STIM_CHIP3_SPI_DR: J2.19, U1.V6 (L23N_T3)
STIM_CHIP4_SPI_DL: J1.22, U1.N17 (L9N_T1_DQS_D13)
STIM_CLK_SHARED: J2.65, U1.B11 (L4N_T0)
STIM_EN_SHARED: J2.63, U1.J6 (IO0)
STIM_START_SHARED: J2.67, U1.B10 (L5P_T0_AD9P)
SWITCHED_3V3: C76.1, C104.1, C106.1, L4.1, TP3.1 (PAD_1), U10.7 (VOUT), U10.8 (VOUT), U10.9 (VOUT), U10.10 (VOUT), U15.6 (VCCB)
VCCADC_1V8: C57.1, L1.2, TP37.1 (PAD_1), U1.J10 (VCCADC_0)
VCCAUX_1V8: C13.1, C14.1, C15.1, C16.1, C17.1, C18.1, C19.1, C20.1, C58.1, C59.1, C60.1, C62.1, C94.1, C95.1, C96.1, C97.1, C98.1, C99.1, C100.1, L1.1, L3.1, R4.1, R17.1, R18.1, R20.1, R21.1, R22.1, R27.1, R38.1, R45.1, R49.1, R53.1, TP5.1 (PAD_1), TP9.1 (PAD_1), U1.E10 (VCCO_0), U1.E11 (VCCBATT_0), U1.G12 (VCCAUX_[5_balls]), U1.H13 (VCCAUX), U1.K13 (VCCAUX), U1.M13 (VCCAUX), U1.P13 (VCCAUX), U1.R10 (VCCO_0), U1.R12 (M0_0), U3.3 (OUT_S), U3.8 (OUT), U3.9 (OUT), U3.10 (OUT), U7.8 (VCC 1.8 V), U8.13 (VCCB_1V8)
VCCINT_1V0: C2.1, C3.1, C4.1, C5.1, C6.1, C7.1, C8.1, C9.1, C10.1, C11.1, C89.1, C90.1, C91.1, C92.1, C93.1, R1.1, TP4.1 (PAD_1), U1.F7 (VCCINT_1V0), U1.F9 (VCCINT_1V0), U1.F11 (VCCBRAM/VCCINT_[21_balls]), U1.G8 (VCCINT_1V0), U1.G10 (VCCBRAM_1V0), U1.H7 (VCCINT_1V0), U1.H9 (VCCINT_1V0), U1.H11 (VCCBRAM_1V0), U1.J8 (VCCINT_1V0), U1.J12 (VCCINT_1V0), U1.K7 (VCCINT_1V0), U1.K11 (VCCINT_1V0), U1.L8 (VCCINT_1V0), U1.L12 (VCCINT_1V0), U1.M7 (VCCINT_1V0), U1.M11 (VCCINT_1V0), U1.N8 (VCCINT_1V0), U1.N10 (VCCINT_1V0), U1.N12 (VCCINT_1V0), U1.P9 (VCCINT_1V0), U1.P11 (VCCINT_1V0), U2.3 (OUT_S), U2.8 (OUT), U2.9 (OUT), U2.10 (OUT)
VCCO_1V5: C22.1, C23.1, C24.1, C25.1, C26.1, C27.1, C28.1, C29.1, C30.1, C31.1, C32.1, C33.1, C34.1, C35.1, C36.1, C37.1, C38.1, C39.1, C40.1, C42.1, C61.1, C63.1, C101.1, C105.1, C107.1, R7.1, R19.1, R25.1, R48.1, R50.1, R58.1, TP6.1 (PAD_1), U1.A16 (VCCO), U1.B13 (VCCO), U1.C10 (VCCO), U1.D17 (VCCO), U1.E14 (VCCO), U1.G18 (VCCO), U1.H15 (VCCO), U1.L6 (VCCO), U1.L16 (VCCO), U1.M3 (VCCO), U1.P7 (VCCO), U1.P17 (VCCO), U1.R4 (VCCO), U1.R14 (VCCO), U1.T1 (VCCO), U1.T11 (VCCO), U1.U8 (VCCO), U1.U18 (VCCO), U1.V5 (VCCO), U1.V15 (VCCO), U4.3 (OUT_S), U4.8 (OUT), U4.9 (OUT), U4.10 (OUT), U8.5 (DIR3_H), U8.14 (VCCA_1V5), U8.15 (DIR1_H), U8.16 (DIR2_H), U14.6 (VCC_1V5), U15.1 (VCCA), U15.5 (DIR)
VIN_3V3: C1.1, C12.1, C21.1, C44.1, C48.1, C75.1, C82.1, C83.1, C85.1, C102.1, C103.1, C208.1, J2.68, J2.69, J2.70, R3.1, R9.1, R43.1, R47.1, R59.1, TP2.1 (PAD_1), U2.4 (EN), U2.13 (IN), U2.14 (IN), U3.13 (IN), U3.14 (IN), U4.13 (IN), U4.14 (IN), U5.4 (BIAS), U6.4 (BIAS), U10.3 (VCC), U10.6 (VIN), U10.11 (VIN), U11.5 (VCC_3V3), U12.4 (VDD_3V3), U13.13 (IN), U13.14 (IN), U16.3 (OUT_S), U16.8 (OUT), U16.9 (OUT), U16.10 (OUT)
VIN_5V: C206.1, C207.1, C209.1, J1.32, J3.19 (5V_IN), TP14.1 (PAD_1), U16.4 (EN), U16.13 (IN), U16.14 (IN)

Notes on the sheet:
Bring-up test pads V54 (TP15-TP47), 18 Nov 2026
Top face (L1): reachable with the board stacked
Bottom face (L14): standalone bench tests only (faces the FPGA-LDO A board)
Bottom face (L14), continued
Function: bare 0.6 mm copper pads so this board can be checked on its own with an oscilloscope: rails that had no pad (1V4_GTP_IN, VCCADC_1V8, OSC125_3V3), clocks (CLK25_PL, configuration CCLK, ASIC2 32 MHz), resets, enables and power-good signals, configuration flash DQ0, ASIC 7/8 SPI clock and la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
Source / changes: designed by Claude for bring-up probing per Howard's 18 Nov 2026 request (his professor asked for oscilloscope test pads on every board); not a manufacturer circuit. Adds 33 TestPoint symbols (LearningFPGA:Copper_Probe, footprint TestPoint_Pad_D0.6mm_Edge_NoPaste, the same as TP1-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
Function: break-off test frame header (test frame V9). 9 short tracks carry these existing nets to the board edge, where they cross the frame tabs to a 2x8 2.54 mm box header on the frame: VIN_5V (J1.32) is the bench power INPUT, with GND (TP20, TP21, J1.30) as its return; VIN_3V3 (J2.69) is the 3.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
Source / changes: designed by Claude on Howard's 18 Nov 2026 request, after the photo of the Open Ephys ONIX NRIC1384 headstage test board; not a manufacturer circuit. Layout 14 layers V11 adds only tracks: 6 on L1 straight south from TP10, TP20, TP11, TP6, TP21, TP9 (0.10 mm, 0.75-0.81 mm; TP10, T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
1. Function: MP5077 enables the local3.3V clock/support branch after core PG. VIN_3V3 from U16 (5 V cable input) feeds FPGA buck inputs and GTP LDO BIAS directly. The carrier port switch limits cable current.
2. Source / changes: Trenz TE0714-04-42I-7-L REV04(20Dec2022),p9 Q1/R52/C1/input-output bypass copied: https://www.trenz-electronic.de/trenzdownloads/Trenz_Electronic/Modules_and_Module_Carriers/3x4/TE0714/REV04/Documents/SCH-TE0714-04-42I-7-L.PDF MPS MP5077 Rev1.2(15Aug2023),p2 pinout,pp11-14 limi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
1. Function: U15 passes M15 EN_GTPWR_1V5 to U13 EN at3.3V. R58=4.99k pulls A HIGH by default; DIR HIGH selects A-to-B. R57=10k pulls B LOW when translator power is absent. C105/C106=100nF bypass both supply rails.
2. Source / changes: Codex voltage adaptation of Trenz TE0714 REV04 pp5,6,9: M15 EN_GTPWR,4.99k default pullup and two cascaded open-drain inverters. https://www.trenz-electronic.de/trenzdownloads/Trenz_Electronic/Modules_and_Module_Carriers/3x4/TE0714/REV04/Documents/SCH-TE0714-04-42I-7-L.PDF Tren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
1. Function: U1 / J1 / J2: Route 121 FPGA lines (121 signals for eight 1.5 V ASICs; J1.36 was a spare until V56) through two 70-contact Hirose DF40C-70DS mezzanines with 15 grounds (J1 14/15/27/30/34/41/50/66, J2 14/15/27/34/41/50/66). J2.68-70 carry VIN_3V3 and J1.32 carries VIN_5V (unused provisi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
2. Source / changes: Codex custom ASIC interface. V8 FPGA-side pin remap (Howard approved 2 Nov 2026): ASIC groups moved to the bank nearest their connector, each returned clock on a clock-capable pin. V11 (Howard approved 2 Nov 2026): J1/J2 DF40C-60DS to DF40C-70DS (Hirose DF40 catalog Jun 2024 p.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
1. Function: J3 carries the GT recording pair (3/5, TX0 FPGA->XEM, DC to the cable), the LVDS 32 MHz cable clock (6/8 -> R61 -> P14/R15 MRCC), LVDS command with SYNC folded in (9/11 -> R62 -> M14/N14), a separate LVDS SYNC (12/14 -> R64 -> B9/A9, V44), JTAG and 5 V (19 -> VIN_5V -> U16); U17/U18 cl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
2. Source / changes: Codex custom HDMI map. V38 (Howard 5 Nov 2026, cable clock/SYNC/GT command), cable map confirmed with Dr. Xie: 6/8 and 9/11 move from GTP TX1/TX2 (C202-C205 removed; F2/F1/D2/D1 open per UG482 v1.9 p236) to bank 14 LVDS_25 inputs; 12/14 move from V3/V2 DIFF_SSTL15 to GTP RX0 (g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
1. Function: U4: Generate1.5V for ASIC banks14/15/34, U8 A-side, Y2 and U15 A-side; enabled by U3 PG (PG_AUX_1V8; U3 internal 440k pull-up). PG participates in reset readiness.
2. Source / changes: Codex adaptation of Trenz p9 buck structure: separate1.5V converter retained for required ASIC interface. R7/R8 divider remains150k/100k,0.1%; V52/V53 (Howard 16 Nov 2026): EN from U3 PG (internal 440k pull-up; R65 dropped in V53, no layout room), VCCO follows VCCAUX (DS181 p.8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
1. Function: ASIC-bank bypass: Bank14 C24-C29+C101=3x4.7u+4x470n; Bank15 C30-C35=2x4.7u+4x470n; Bank34 C36-C40+C107=3x4.7u+3x470n. C42=47u shared1.5V bulk.
2. Source / changes: Trenz p7 bank populations restored: addedC1014.7u; removed extraC41470n. Common3.3V Bank0/14 network split for our1.8V/1.5V domains. https://www.trenz-electronic.de/trenzdownloads/Trenz_Electronic/Modules_and_Module_Carriers/3x4/TE0714/REV04/Documents/SCH-TE0714-04-42I-7-L.PDF 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
1. Function: L1/L2/C57/C58: Filter AUX1.8V for unused XADC; analog/reference inputs grounded to GNDADC.
2. Source / changes: Trenz p7 L10/L11/C62/C63 circuit retained with exact ferrites. Custom connector omits Trenz external ADC pair; unused-input grounding retained. https://www.trenz-electronic.de/trenzdownloads/Trenz_Electronic/Modules_and_Module_Carriers/3x4/TE0714/REV04/Documents/SCH-TE0714-04-4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
1. Function: U7/U8: 8MiB 1.8V SPI NOR flash (Winbond W25Q64JWUUIQ, USON-8 4x3mm, 0.8mm pitch) and SN74AVC4T774RSV SPIx1 translation. Bank14 remains1.5V; initialCONFIGRATE3MHz/QE=1 fixed/3-byte addresses.
2. Source / changes: Part changed 24 Nov 2026 (Howard): W25Q128JWYIQ WLCSP-21 -> W25Q64JWUUIQ USON-8 4x3mm (JLC C6604692); JLC could not buy the WLCSP. Same JW family, pad order and Q option (QE=1 fixed: WP#/HOLD# functions off); capacity now 64Mbit. W25Q64JW Rev.E 10Mar2021: pads Fig.1b p5, outlin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
1. Function: Y2: 25MHz fabric clock drives T14 MRCC (bank 14, 1.5V). L3 filters the 1.8V VCCAUX supply; C88=100nF; R44 150R / R63 680R attenuate and damp the output.
2. Source / changes: Trenz p5 U8/L2/C24/R23 structure adapted: SiT1615 1.5V replaces SiT8008 1.8V; CLK25 used N3 SRCC until V44; V45 (Howard 10 Nov 2026, Claude): T14 MRCC, R44/R63 not moved. C88 retained100n per SiTime; R44 exact Trenz RC0201FR-0733RL restored. https://www.trenz-electronic.de/tren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
1. Function: GTP bypass C51-C56: each analog rail now4.7uF+2x470nF. R16=100R connects MGTRREF to MGTAVTT.
2. Source / changes: Trenz p7 nominal/value/package/tolerance restored: C52/C53/C55/C56 100n->470n; C51/C54 4.7u20%; R16 selected100R0.1%25ppm ERA1A meets source100R1%TK100 class. Selected compatible Murata/Yageo candidates; Trenz exact MPNs not all disclosed. https://www.trenz-electronic.de/trenzd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
1. Function: Y1 supplies125MHz LVDS through C78/C79=100nF to REFCLK1P/N. L4 filters switched3.3V; C80=470nF and C81=100nF bypass it. The REFCLK input's internal 100R is the only load; OE HIGH, pin2 NC.
2. Source / changes: Trenz TE0714-04-42I-7-L REV04 p6:125MHz LVDS U2, L1 ferrite, C10=470nF, R1=100R and C134/C135=100nF coupling. https://www.trenz-electronic.de/trenzdownloads/Trenz_Electronic/Modules_and_Module_Carriers/3x4/TE0714/REV04/Documents/SCH-TE0714-04-42I-7-L.PDF Adapted by Codex: Y1=AX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
01. FPGA I/O + ASIC INTERFACES + 25 MHz CLOCK | Trenz p5
02. GTP CHANNELS + 125 MHz REFERENCE | Trenz p6
03. FLASH + SPI TRANSLATION | Trenz p6 adaptation
04. CONFIGURATION + RESET OUTPUTS | Trenz p7 roles
05. FPGA SUPPLY PINS + BYPASS + XADC | Trenz p7
06. REGULATORS + READINESS SUPERVISOR | Trenz p9 roles
1. Function: U1 configuration: Master SPI001,CFGBVS GND, Bank0/JTAG1.8V; ASIC banks1.5V. PROGRAM_B and INIT_B reset independently. VCCBATT E11 now AUX1.8V.
2. Source / changes: Trenz p7 values restored where compatible: R19/R22=4.99k (R17/R18 too until V55); E11 GND->AUX. Mode ties/1.8V rails and x1 flash remain agreed adaptations. https://www.trenz-electronic.de/trenzdownloads/Trenz_Electronic/Modules_and_Module_Carriers/3x4/TE0714/REV04/Documents/SC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
1. Function: Bank0 bypass C59 (footprint DNP, V49),C94-C100:3x4.7uF+4x470nF fitted at1.8V, separate from1.5V Bank14.
2. Source / changes: Codex split of Trenz p7 shared Bank0/14 network to preserve agreed voltage domains; addedC94-C100, C59 exact Trenz CC0805MKX5R5BB476. https://www.trenz-electronic.de/trenzdownloads/Trenz_Electronic/Modules_and_Module_Carriers/3x4/TE0714/REV04/Documents/SCH-TE0714-04-42I-7-L.PDF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

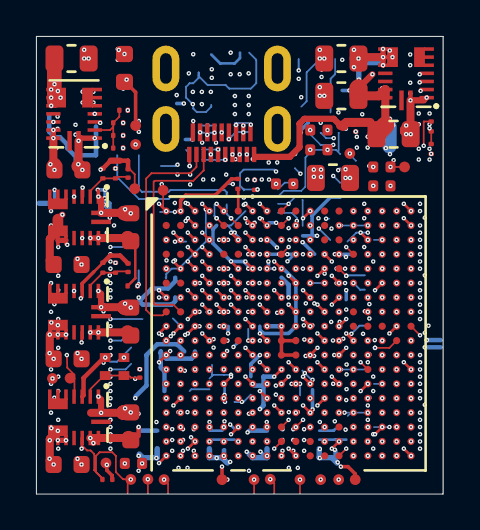
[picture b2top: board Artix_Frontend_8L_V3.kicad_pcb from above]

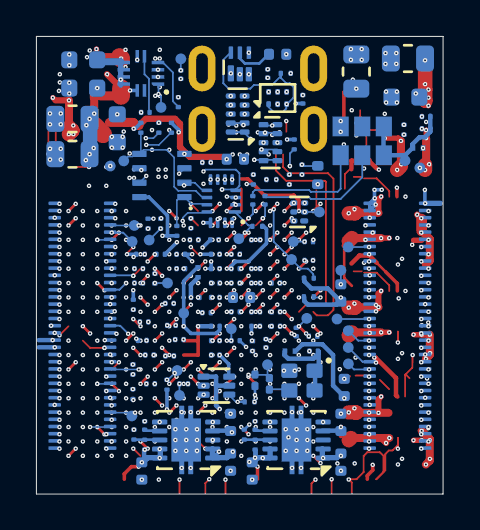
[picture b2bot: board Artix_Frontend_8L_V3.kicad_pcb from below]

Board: 14 copper layers, 22.6 x 25.4 mm, 218 parts (152 on the bottom side), 190 nets.

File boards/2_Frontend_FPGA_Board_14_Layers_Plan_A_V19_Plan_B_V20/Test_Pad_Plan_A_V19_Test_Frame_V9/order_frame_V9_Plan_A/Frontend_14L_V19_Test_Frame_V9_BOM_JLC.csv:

Comment,Designator,Footprint,JLCPCB Part #
22uF GRM188R60J226MEA0D,"C1,C2,C12,C13,C21,C22,C85,C86,C75,C76,C102,C104",C_0603_1608Metric,C77042
22pF GRM0335C1H220GA01D,"C3,C14,C23,C87",C_0201_GRM03_Murata_0p22Gap,C161417
4.7uF GRM035R60J475ME15D,"C5,C6,C25,C36,C37,C51,C54,C96,C107",C_0201_GRM03_Murata_0p22Gap,C335103
470nF GRM033R60J474ME90D,"C7,C8,C9,C11,C18,C19,C20,C26,C27,C28,C29,C32,C33,C34,C35,C38,C39,C40,C52,C53,C55,C56,C57,C58,C80,C91,C92,C93,C97,C98,C99,C100,C103",C_0201_GRM03_Murata_0p22Gap,C88915
47uF GRM21BR60J476ME15L,C10,C_0805_2012Metric,C77072
47uF CC0805MKX5R5BB476,C15,C_0805_2012Metric,C109461
47uF GRM219R60J476ME44D,C42,C_0805_2012Metric,C471380
4.7uF GRM155R60J475ME47D,"C16,C17,C24,C30,C31,C43,C44,C45,C47,C48,C49,C90,C94,C95,C101",C_0402_1005Metric,C82453
10nF GRM033R71A103KA01D,"C46,C50",C_0201_GRM03_Murata_0p22Gap,C76941
100nF GRM033R61A104KE15D,"C60,C63,C78,C79,C81,C82,C83,C88,C105,C106,C209",C_0201_GRM03_Murata_0p22Gap,C76934
1uF GRM155C81A105KA12D,"C61,C84",C_0402_1005Metric,C162161
220nF GRM033R60J224KE15D,C62,C_0201_GRM03_Murata_0p22Gap,C76931
22nF GRM033R61C223KE84D,C77,C_0201_GRM03_Murata_0p22Gap,C161473
22uF GRM21BR61A226ME44L,"C206,C207,C208",C_0805_2012Metric,C441864
DF40C-70DS-0.4V(51) DF40C-70DS-0.4V(51),"J1,J2",Hirose_DF40C-70DS-0.4V_2x35_P0.4mm,C294854
Micro-HDMI 467651001 467651001,J3,Molex_MicroHDMI_46765_1xxx,C563878
MPZ0603S121HT000 MPZ0603S121HT000,"L1,L2,L3,L4",TDK_MPZ0603S121HT000_0201_Land_0p25x0p30_Gap0p30,C695597
200k RC0201FR-07200KL,"R1,R4,R5,R41,R55,R59",R_0201_ERA1A_Panasonic_0p30Gap,C138163
301k RC0201FR-07301KL,R2,R_0201_ERA1A_Panasonic_0p30Gap,C77621
4.99k RC0201FR-074K99L,"R3,R9,R19,R22,R38,R43,R58",R_0201_ERA1A_Panasonic_0p30Gap,C273265
150k RT0402BRD07150KL,R7,R_0402_TE_CPF_Reflow_0p50Gap,C852538
100k CPF0402B100KE1,R8,R_0402_TE_CPF_Reflow_0p50Gap,C4015434
1.3k 0201WMF1301TEE,R10,R_0201_ERA1A_Panasonic_0p30Gap,C473569
4.99k RT0201BRD074K99L,"R11,R14",R_0201_ERA1A_Panasonic_0p30Gap,C852255
2.49k TNPW02012K49BEED,R13,R_0201_ERA1A_Panasonic_0p30Gap,C1870640
100R ERA1AEB101C,"R16,R61,R62,R64",R_0201_ERA1A_Panasonic_0p30Gap,C490806
4.7k RC0201FR-074K7L,"R17,R18,R20,R21,R49,R50",R_0201_ERA1A_Panasonic_0p30Gap,C138135
470R RC0201FR-07470RL,R25,R_0201_ERA1A_Panasonic_0p30Gap,C295802
1k RC0201FR-071KL,R27,R_0201_ERA1A_Panasonic_0p30Gap,C138165
24k 0201WMF2402TEE,R37,R_0201_ERA1A_Panasonic_0p30Gap,C270353
150k RC0201FR-07150KL,R42,R_0201_ERA1A_Panasonic_0p30Gap,C274346
150R RC0201FR-07150RL,R44,R_0201_0603Metric,C295773
4.64k RT0402BRD074K64L,R45,R_0402_1005Metric,C705067
10k ERA1AEB103C,"R46,R47,R48",R_0201_ERA1A_Panasonic_0p30Gap,C490808
47k RC0201FR-0747KL,"R51,R52,R53",R_0201_ERA1A_Panasonic_0p30Gap,C138139
22k RC0201FR-0722KL,R54,R_0201_ERA1A_Panasonic_0p30Gap,C474416
10k RC0201FR-0710KL,R57,R_0201_ERA1A_Panasonic_0p30Gap,C106225
44.2k AC0201FR-0744K2L,R60,R_0201_ERA1A_Panasonic_0p30Gap,C226551
680R AC0201FR-07680RL,R63,R_0201_0603Metric,C4103963
XC7A35T-2CSG325C,U1,Xilinx_CSG325,C1521720
MPM3833CGRH MPM3833CGRH-Z,"U2,U3,U4,U13,U16",MPS_QFN-18_2.5x3.5mm_MPM3833C,C6306422
TPS74801DRCR TPS74801DRCR,"U5,U6",VSON-10-1EP_3x3mm_P0.5mm_EP1.65x2.4mm,C105263
W25Q64JWUUIQ W25Q64JWUUIQ,U7,Winbond_USON8_4x3mm_UU,C6604692
SN74AVC4T774RSVR SN74AVC4T774RSVR,U8,TI_RSV_UQFN16_1.8x2.6mm_P0.4mm,C779392
MP5077GG-Z MP5077GG-Z,U10,MPS_MP5077_QFN12_2x2mm_P0.4mm,C3215595
"74AUP2G07GM 74AUP2G07GM,115",U11,Nexperia_SOT886_XSON6_1x1.45mm,C546047
TPS389001 TPS389001DSER,U12,TI_DSE0006A_WSON6_1p5x1p5_P0p5_Manufacturer,C1509297
SN74AUP1G14 SN74AUP1G14DRYR,U14,Texas_USON-6_1x1.45mm_P0.5mm_SMD,C2865597
SN74AXC1T45DRLR SN74AXC1T45DRLR,U15,SOT-563,C191003
TPD4E02B04DQAR TPD4E02B04DQAR,"U17,U18",USON-10_2.5x1.0mm_P0.5mm,C106794
AX3DAF1-125.0000T3 AX3DAF1-125.0000,Y1,Abracon_AX3_3225_6pin,C1670018
OT201625MJBA4SL OT201625MJBA4SL,Y2,YXC_SMD2016-4P_2.0x1.6mm,C669080
Box header 2x8 2.54mm BOOMELE 2.54-2*8P (through-hole; on the test frame),JT1,IDC-Header_2x08_P2.54mm_Vertical,C3406
